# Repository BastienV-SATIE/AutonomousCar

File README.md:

# AutonomousVehicle

All the source file to construct your own autonomous 1:10 vehicle.
MDPI and ACS Style
Vincke, B.; Rodriguez Florez, S.; Aubert, P. An Open-Source Scale Model Platform for Teaching Autonomous Vehicle Technologies. Sensors 2021, 21, 3850. https://doi.org/10.3390/s21113850

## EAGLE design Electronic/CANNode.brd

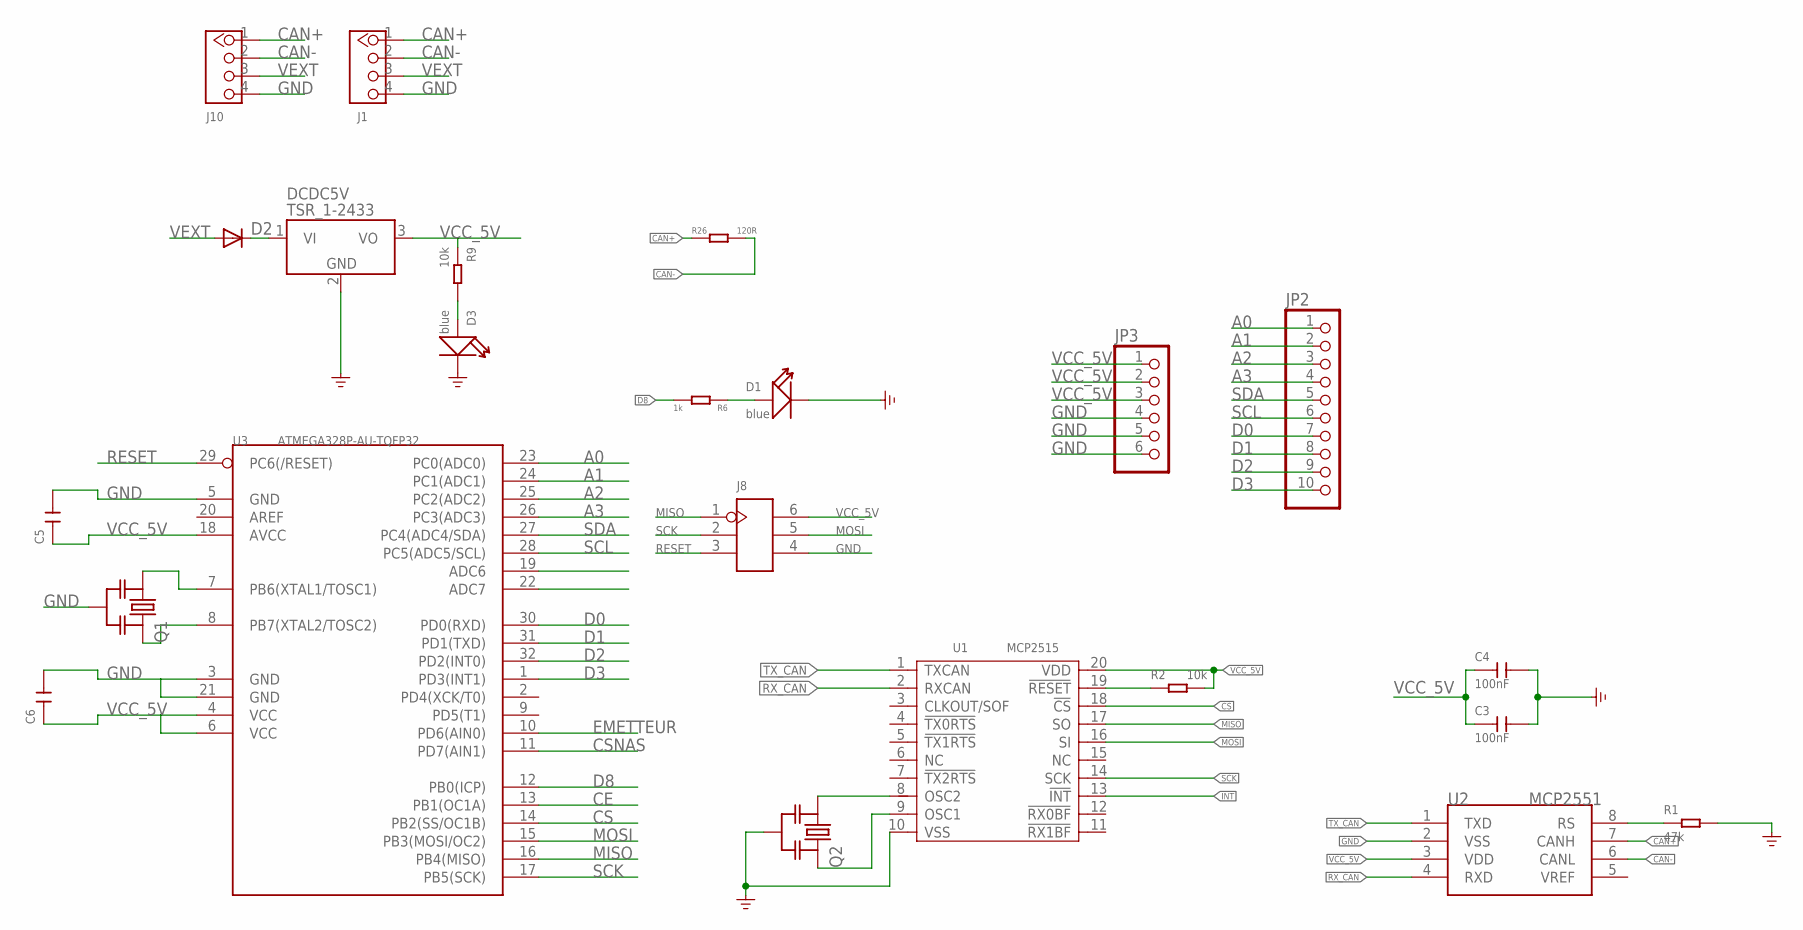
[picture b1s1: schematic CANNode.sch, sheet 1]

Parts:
C3, C4: 100nF; C0805
C5, C6: CAP-0805; C0805
D1, D3: blue; LED-0805
D2: DIODE-SOD323-W; SOD323-W
DCDC5V: TSR_1-2433; TSR-1
J1, J10: 320110033; HW4-2.0
J8: HEADER-2X3P-2.54; H2X3-2.54
JP2: PINHD-1X10; 1X10
JP3: PINHD-1X6; 1X06
Q1, Q2: RESONATOR-MURATACST_CE; RESONATOR_MURATA2
R1: 47k; R0805
R2: 10k; R0603
R6: 1k; R0805
R9: 10k; R0805
R26: 120R; R0805
U1: MCP2515; TSSOP20-0.65-6.5X4.4MM
U2: MCP2551; SOIC8-6.0
U3: ATMEGA328P-AU-TQFP32; TQFP32-0.8-7X7MM

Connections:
A0: JP2.1, U3.23 (PC0(ADC0))
A1: JP2.2, U3.24 (PC1(ADC1))
A2: JP2.3, U3.25 (PC2(ADC2))
A3: JP2.4, U3.26 (PC3(ADC3))
CAN+: J1.1, J10.1, R26.1, U2.7 (CANH)
CAN-: J1.2, J10.2, R26.2, U2.6 (CANL)
CE: U3.13 (PB1(OC1A))
CS: U1.18 (!CS), U3.14 (PB2(SS/OC1B))
CSNAS: U3.11 (PD7(AIN1))
D0: JP2.7, U3.30 (PD0(RXD))
D1: JP2.8, U3.31 (PD1(TXD))
D2: JP2.9, U3.32 (PD2(INT0))
D3: JP2.10, U3.1 (PD3(INT1))
D8: R6.2, U3.12 (PB0(ICP))
EMETTEUR: U3.10 (PD6(AIN0))
GND: C3.2, C4.2, C5.2, C6.2, D1.-, D3.-, DCDC5V.2 (GND), J1.4, J8.4, J10.4, JP3.4, JP3.5, JP3.6, Q1.2, Q2.2, R1.2, U1.10 (VSS), U2.2 (VSS), U3.3 (GND), U3.5 (GND), U3.21 (GND)
INT: U1.13 (!INT)
MISO: J8.1, U1.17 (SO), U3.16 (PB4(MISO))
MOSI: J8.5, U1.16 (SI), U3.15 (PB3(MOSI/OC2))
unnamed: Q1.1, U3.7 (PB6(XTAL1/TOSC1))
unnamed: Q1.3, U3.8 (PB7(XTAL2/TOSC2))
unnamed: D3.+, R9.2
unnamed: D1.+, R6.1
unnamed: Q2.1, U1.8 (OSC2)
unnamed: Q2.3, U1.9 (OSC1)
unnamed: R1.1, U2.8 (RS)
RESET: J8.3, U3.29 (PC6(/RESET))
RST_N: R2.1, U1.19 (!RESET)
RX_CAN: U1.2 (RXCAN), U2.4 (RXD)
SCK: J8.2, U1.14 (SCK), U3.17 (PB5(SCK))
SCL: JP2.6, U3.28 (PC5(ADC5/SCL))
SDA: JP2.5, U3.27 (PC4(ADC4/SDA))
TX_CAN: U1.1 (TXCAN), U2.1 (TXD)
VCC_5V: C3.1, C4.1, C5.1, C6.1, DCDC5V.3 (VO), J8.6, JP3.1, JP3.2, JP3.3, R2.2, R9.1, U1.20 (VDD), U2.3 (VDD), U3.4 (VCC), U3.6 (VCC), U3.18 (AVCC)
VEXT: D2.A, J1.3, J10.3
VI: D2.C, DCDC5V.1 (VI)

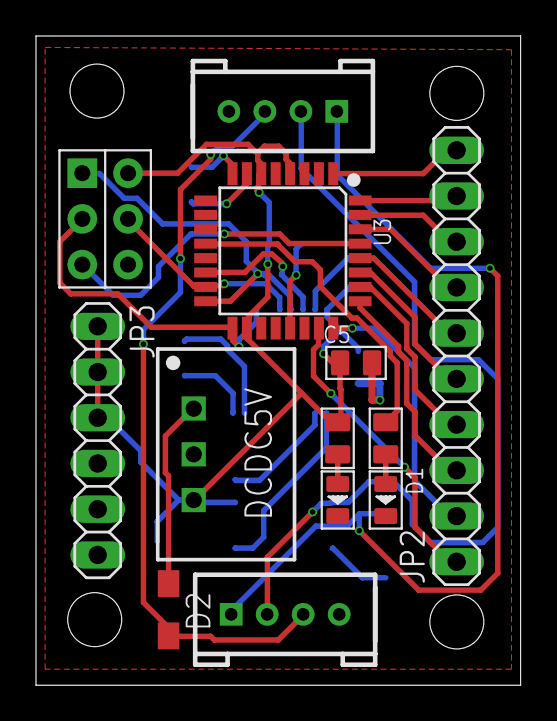
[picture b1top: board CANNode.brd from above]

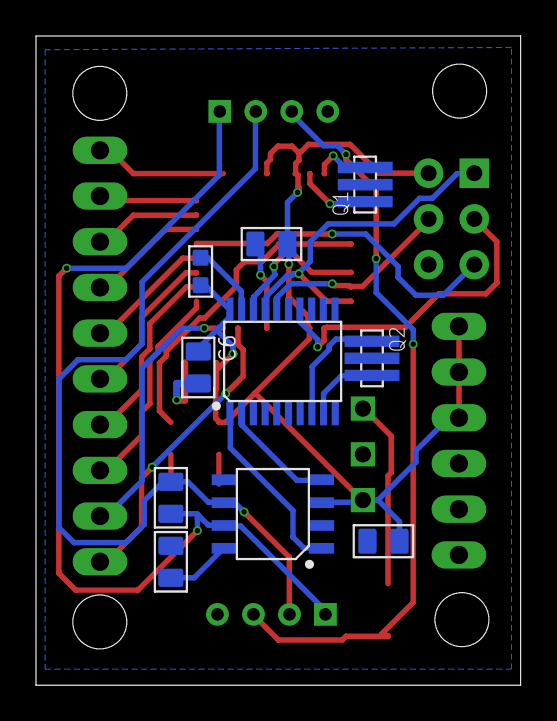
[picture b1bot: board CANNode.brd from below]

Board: 2 copper layers, 26.9 x 36.1 mm, 23 parts (10 on the bottom side), 32 nets.

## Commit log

2021-05-18 Create d
2021-05-18 Create ff
2021-05-18 Create fz

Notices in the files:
parts and their libraries:
m-pad-2.1: License : GNU General Public License version 2 (see bottom)
